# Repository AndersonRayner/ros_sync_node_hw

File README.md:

# ROS Sync Node Hardware

Breaks out a [Waveshare RP2040-Zero](https://www.waveshare.com/rp2040-zero.htm) with 0.1" header pins for use as a ROS-enabled hardware sync node.

# Requirements
## KiCAD Files
Make sure to clone recursively so that you have the required libraries

```
git clone git@github.com:AndersonRayner/ros_sync_node_hw.git --recursive
```

Everything runs using kicad so you'll need that too.

## Arduino
### Add the Board Definition
Support in Arduino for the RP2040-Zero requires adding the board definition to the Boards Manager.
Add the URL
```
https://github.com/earlephilhower/arduino-pico/releases/download/global/package_rp2040_index.json
```
to `File > Preferences > Additional Boards Manager URLs`.

### Install the Toolchain
Open up the boards manager `Tools > Board > Boards Manager` and install `Raspberry Pi Pico/RP2040` by Earle F. Philhower, III.

### Compile Software
The software designed for this board to allow it to act as a ROS sync node is available at [ros_sync_node](https://github.com/AndersonRayner/ros_sync_node).
Compile and upload it as `Tools > Board > Raspberry Pi RP2040 Boards > Raspberry Pi Pico`.

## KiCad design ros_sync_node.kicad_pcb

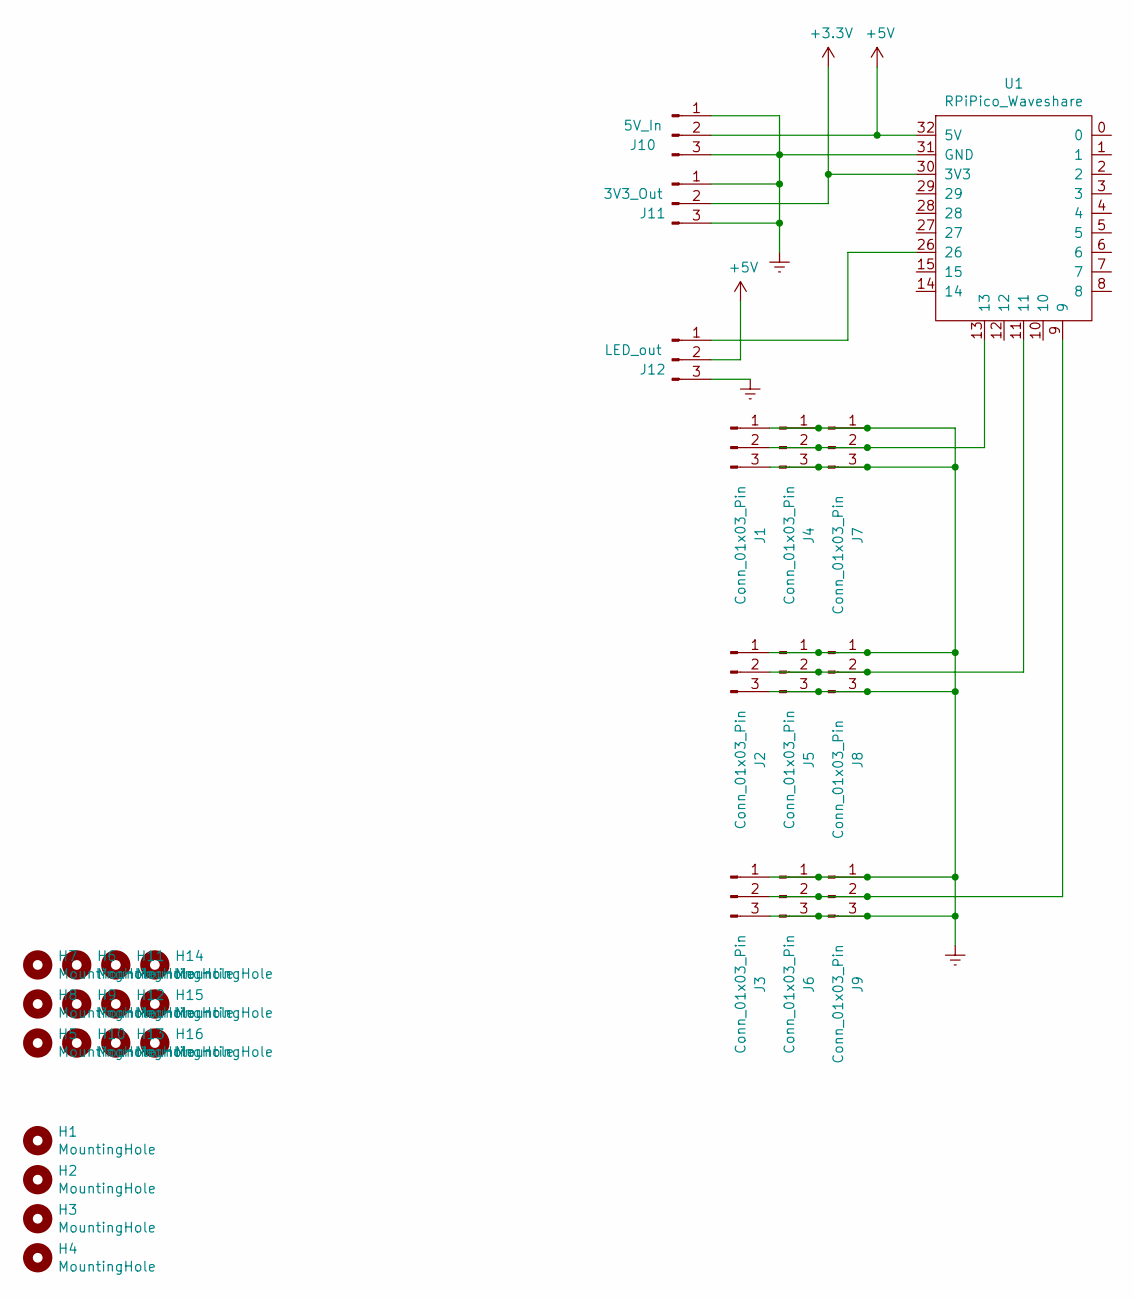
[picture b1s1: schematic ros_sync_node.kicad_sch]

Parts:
H1, H2, H3, H4: MountingHole; MountingHole_3.2mm_M3
H5, H6, H7, H8, H9, H10, H11, H12, H13, H14, H15, H16: MountingHole; OSHTab
J1, J2, J3, J4, J5, J6, J7, J8, J9: Conn_01x03_Pin; PinHeader_1x03_P2.54mm_Vertical
J10: 5V_In; PinHeader_1x03_P2.54mm_Vertical
J11: 3V3_Out; PinHeader_1x03_P2.54mm_Vertical
J12: LED_out; PinHeader_1x03_P2.54mm_Vertical
U1: RPiPico_Waveshare

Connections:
+3.3V: J11.2, U1.30 (3V3)
+5V: J10.2, J12.2, U1.32 (5V)
Earth: J1.1, J1.3, J2.1, J2.3, J3.1, J3.3, J4.1, J4.3, J5.1, J5.3, J6.1, J6.3, J7.1, J7.3, J8.1, J8.3, J9.1, J9.3, J10.1, J10.3, J11.1, J11.3, J12.3, U1.31 (GND)
unnamed: J1.2, J4.2, J7.2, U1.13
unnamed: J2.2, J5.2, J8.2, U1.11
unnamed: J3.2, J6.2, J9.2, U1.9
unnamed: J12.1, U1.26

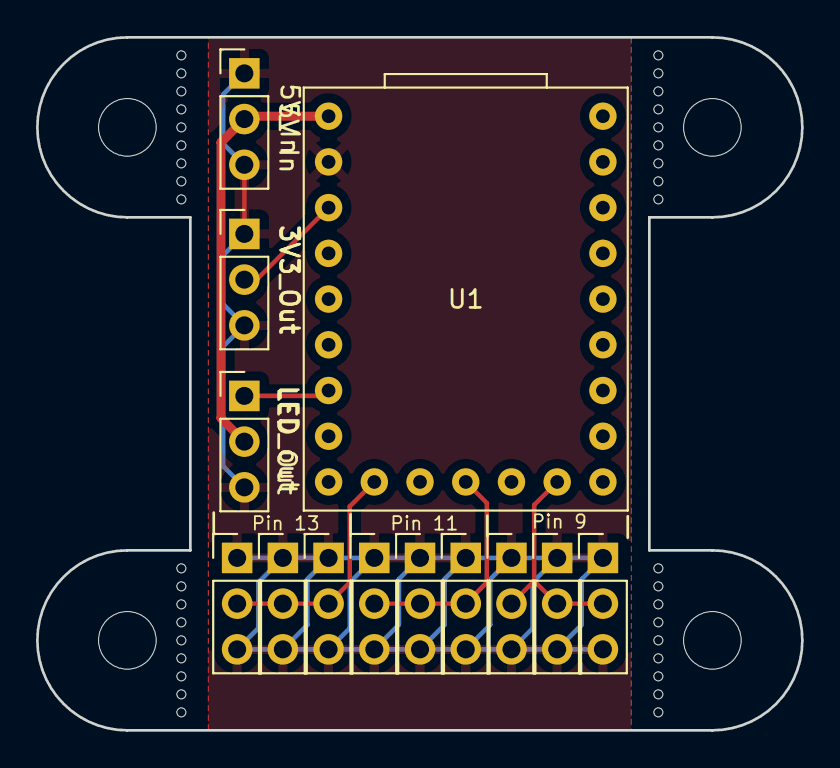
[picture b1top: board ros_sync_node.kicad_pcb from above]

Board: 2 copper layers, 42.5 x 38.5 mm, 29 parts (0 on the bottom side), 7 nets.

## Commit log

2022-02-22 Added mousebites and a readme
2022-02-22 Submodule update
2023-12-21 Added output pin for the neopixels. Update to KiCAD 7
2023-12-21 Fixed some text
2024-05-06 Update git ignore
